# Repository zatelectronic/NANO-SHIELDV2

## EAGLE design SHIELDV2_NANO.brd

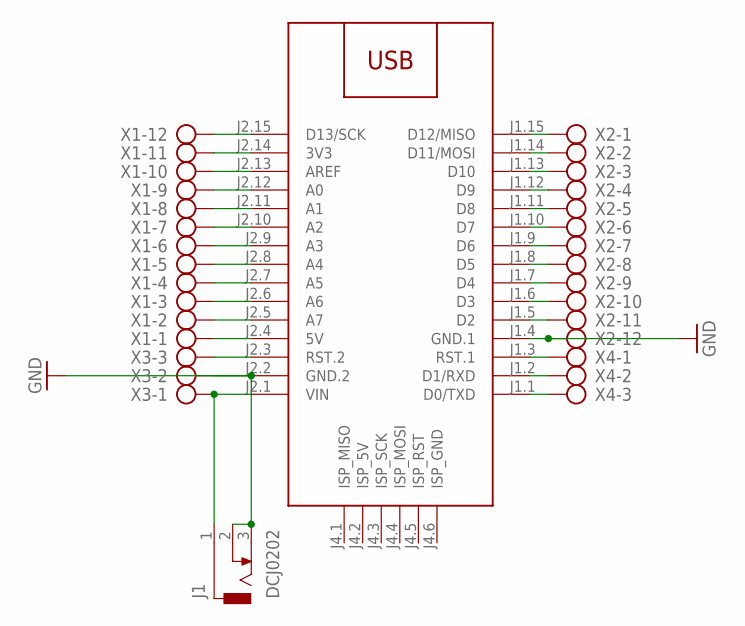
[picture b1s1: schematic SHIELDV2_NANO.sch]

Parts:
J1: DCJ0202
M1: ARDUINO-NANO-3.0#ISP
X1, X2: AK300/12
X3, X4: AK300/3

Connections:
GND: J1.2, J1.3, M1.J1.4 (GND.1), M1.J2.2 (GND.2), X2.12, X3.2
unnamed: M1.J1.3 (RST.1), X4.1
unnamed: J1.1, M1.J2.1 (VIN), X3.1
unnamed: M1.J2.15 (D13/SCK), X1.12
unnamed: M1.J2.14 (3V3), X1.11
unnamed: M1.J2.13 (AREF), X1.10
unnamed: M1.J2.12 (A0), X1.9
unnamed: M1.J2.11 (A1), X1.8
unnamed: M1.J2.10 (A2), X1.7
unnamed: M1.J2.9 (A3), X1.6
unnamed: M1.J2.8 (A4), X1.5
unnamed: M1.J2.7 (A5), X1.4
unnamed: M1.J2.6 (A6), X1.3
unnamed: M1.J2.5 (A7), X1.2
unnamed: M1.J2.4 (5V), X1.1
unnamed: M1.J1.15 (D12/MISO), X2.1
unnamed: M1.J1.14 (D11/MOSI), X2.2
unnamed: M1.J1.13 (D10), X2.3
unnamed: M1.J1.12 (D9), X2.4
unnamed: M1.J1.11 (D8), X2.5
unnamed: M1.J1.10 (D7), X2.6
unnamed: M1.J1.9 (D6), X2.7
unnamed: M1.J1.8 (D5), X2.8
unnamed: M1.J1.7 (D4), X2.9
unnamed: M1.J1.6 (D3), X2.10
unnamed: M1.J1.5 (D2), X2.11
unnamed: M1.J2.3 (RST.2), X3.3
unnamed: M1.J1.2 (D1/RXD), X4.2
unnamed: M1.J1.1 (D0/TXD), X4.3

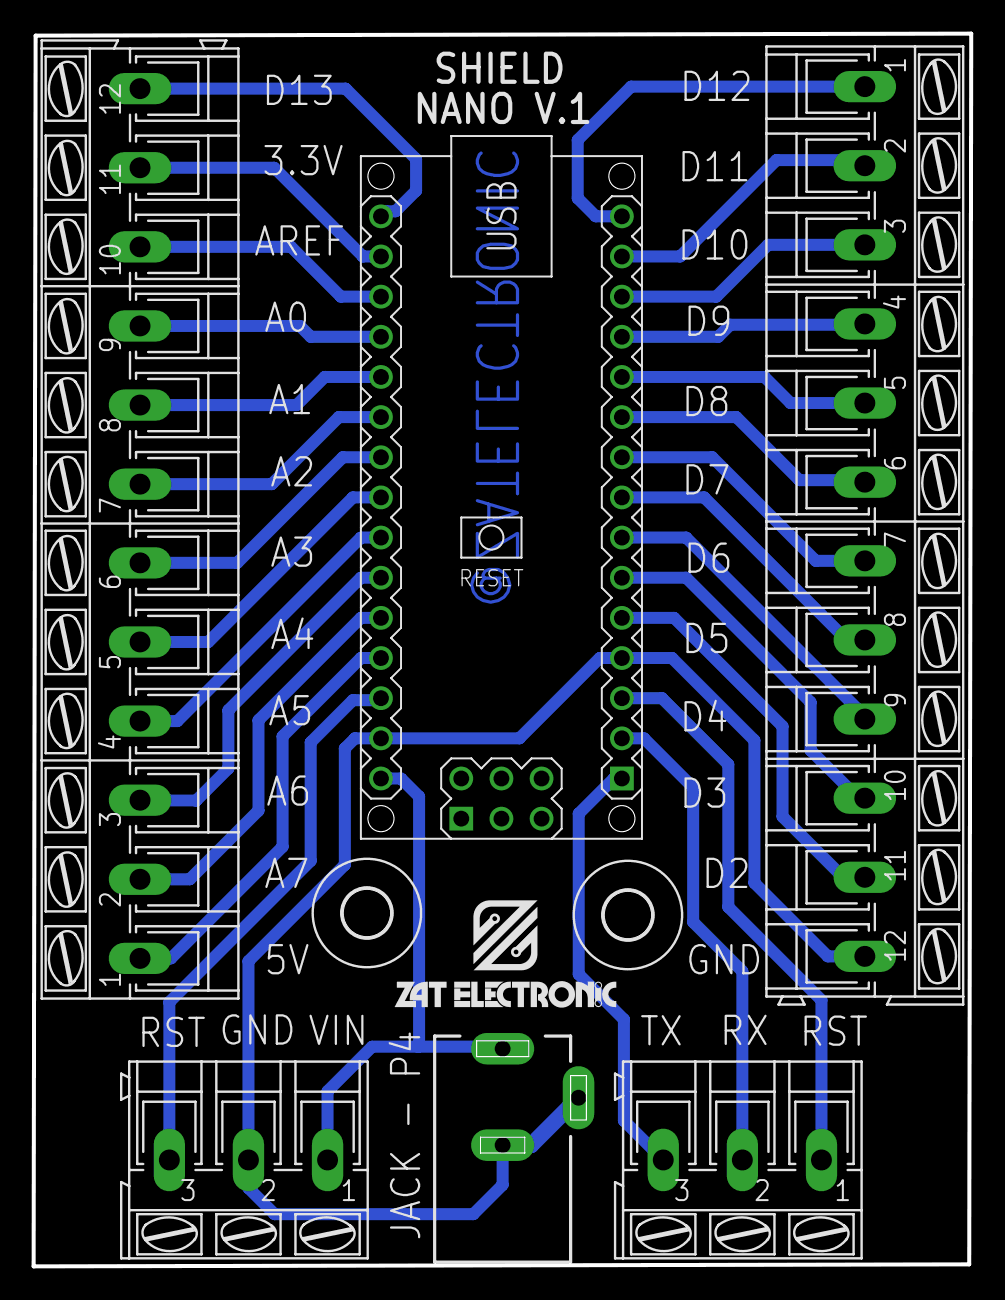
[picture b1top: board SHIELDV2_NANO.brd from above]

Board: 2 copper layers, 59.3 x 78.0 mm, 9 parts (0 on the bottom side), 29 nets.

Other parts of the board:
U$1: ZAT_ESCRITA_0.5
U$2, U$3: 3,0

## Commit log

2021-10-23 PRIMEIRO ENVIO
2021-10-25 ATUALIZAÇÃO

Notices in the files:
parts and their libraries:
ARDUINO MODULOS: Released under the Creative Commons Attribution 4.0 International License: http://creativecommons.org/licenses/by/4.0
